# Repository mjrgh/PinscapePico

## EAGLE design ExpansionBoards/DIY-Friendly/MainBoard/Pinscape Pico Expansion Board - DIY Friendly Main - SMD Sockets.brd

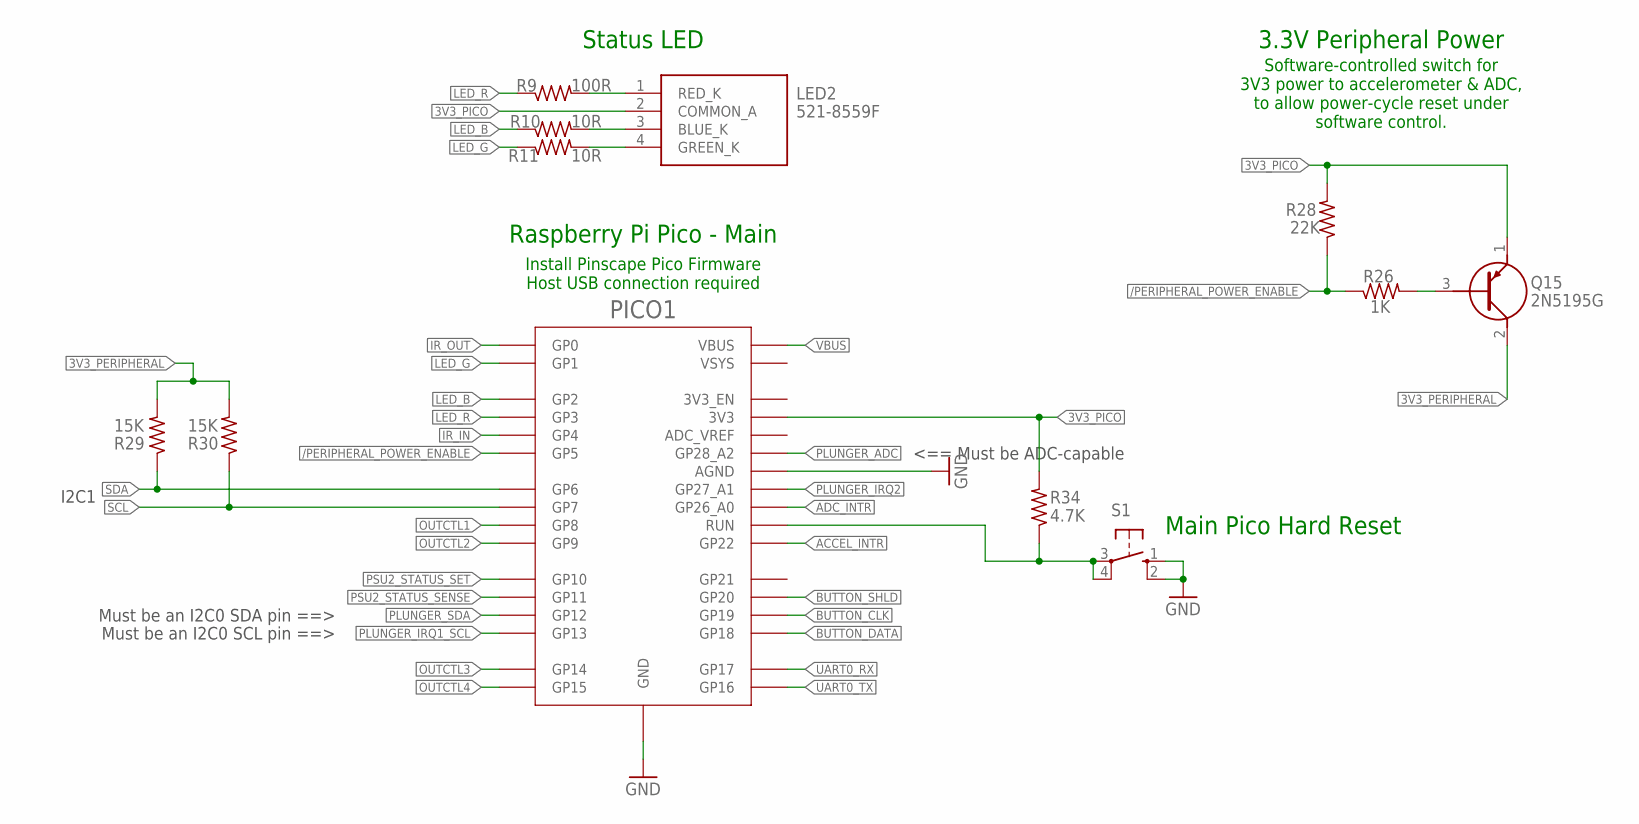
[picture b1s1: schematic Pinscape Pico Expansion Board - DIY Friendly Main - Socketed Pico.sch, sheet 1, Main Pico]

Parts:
LED2: 521-8559F; 5218559F
PICO1: RPI_PICO_NO_DEBUG; RPI_PICO_TH_NO_DEBUG
Q15: 2N5195G; TO229P300X760X1364-3P
R9: 100R; 0204/7; PARTNO 660-MFS1/4DCT52R47R0
R10, R11: 10R; 0204/7; PARTNO 660-MFS1/4DCT52R47R0
R26: 1K; 0204/7; PARTNO 660-MFS1/4DCT52R47R0
R28: 22K; 0204/7; PARTNO 660-MFS1/4DCT52R47R0
R29, R30: 15K; 0204/7; PARTNO 660-MFS1/4DCT52R47R0
R34: 4.7K; 0204/7; PARTNO 660-MFS1/4DCT52R47R0
S1: 10-XX; B3F-10XX

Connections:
3V3_PERIPHERAL: Q15.2 (C), R29.2, R30.2; also elsewhere on the board
3V3_PICO: LED2.2 (COMMON_A), PICO1.3V3, Q15.1 (E), R28.2, R34.2; also elsewhere on the board
LED_B: PICO1.GP2, R10.1; also elsewhere on the board
LED_G: PICO1.GP1, R11.1; also elsewhere on the board
LED_R: PICO1.GP3, R9.1; also elsewhere on the board
unnamed: LED2.1 (RED_K), R9.2
unnamed: Q15.3 (B), R26.2
unnamed: LED2.3 (BLUE_K), R10.2
unnamed: LED2.4 (GREEN_K), R11.2
UART0_RX: PICO1.GP17; also elsewhere on the board
UART0_TX: PICO1.GP16; also elsewhere on the board

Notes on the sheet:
Raspberry Pi Pico - Main
Must be an I2C0 SCL pin ==>
<== Must be ADC-capable
Must be an I2C0 SDA pin ==>
Main Pico Hard Reset
Status LED
3.3V Peripheral Power
Install Pinscape Pico Firmware Host USB connection required
I2C1
Software-controlled switch for 3V3 power to accelerometer & ADC, to allow power-cycle reset under software control.

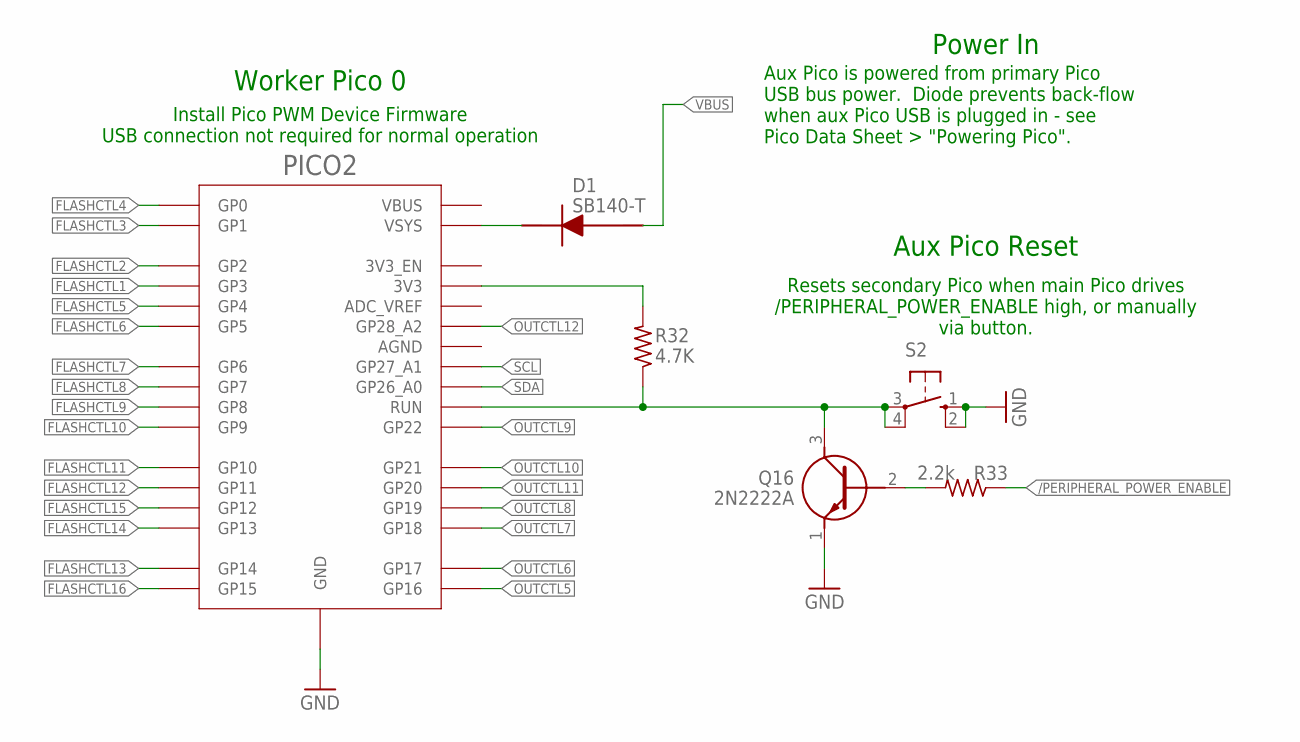
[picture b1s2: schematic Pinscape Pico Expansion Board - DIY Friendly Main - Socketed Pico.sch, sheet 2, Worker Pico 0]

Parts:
D1: SB140-T; DIOAD1408W86L464D236
PICO2: RPI_PICO_NO_DEBUG; RPI_PICO_TH_NO_DEBUG
Q16: 2N2222A
R32: 4.7K; 0204/7; PARTNO 660-MFS1/4DCT52R47R0
R33: 2.2k; 0204/7; PARTNO 660-MFS1/4DCT52R47R0
S2: 10-XX; B3F-10XX

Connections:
unnamed 103: D1.1 (K), PICO2.VSYS; also elsewhere on the board
unnamed: Q16.2 (B), R33.2
unnamed 120: PICO2.3V3, R32.2; also elsewhere on the board

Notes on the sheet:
Install Pico PWM Device Firmware USB connection not required for normal operation
Worker Pico 0
Aux Pico Reset
Resets secondary Pico when main Pico drives /PERIPHERAL_POWER_ENABLE high, or manually via button.
Aux Pico is powered from primary Pico USB bus power. Diode prevents back-flow when aux Pico USB is plugged in - see Pico Data Sheet > "Powering Pico".
Power In

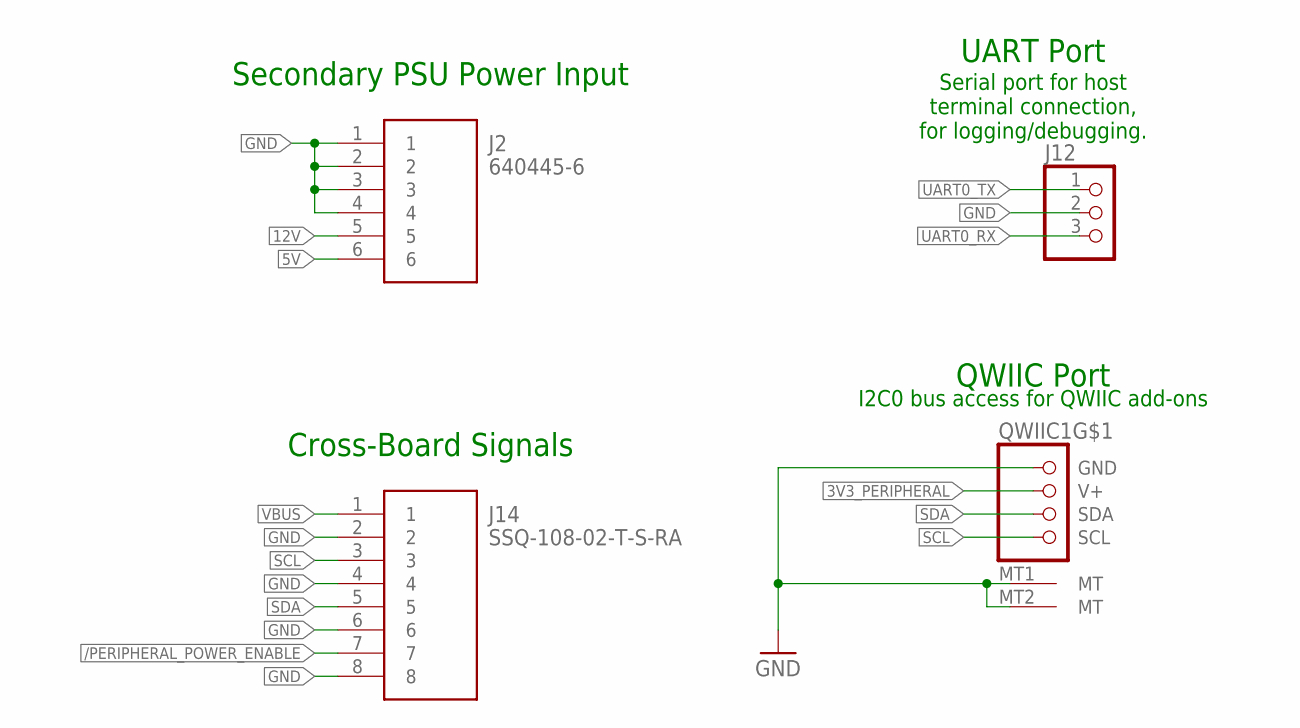
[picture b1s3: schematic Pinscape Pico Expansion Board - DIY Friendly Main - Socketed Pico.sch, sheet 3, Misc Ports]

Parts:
J2: 640445-6; SHDR6W183P0X396_1X6_2377X762X1
J12: PINHD-1X3; 1X03
J14: SSQ-108-02-T-S-RA; RHDRRA8W64P254_1X8_2083X851X24
QWIIC1: QWIIC; JST_SH4

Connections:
3V3_PERIPHERAL: QWIIC1.2 (V+); also elsewhere on the board
5V: J2.6; also elsewhere on the board
12V: J2.5; also elsewhere on the board
UART0_RX: J12.3; also elsewhere on the board
UART0_TX: J12.1; also elsewhere on the board

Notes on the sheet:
UART Port
Serial port for host terminal connection, for logging/debugging.
Secondary PSU Power Input
Cross-Board Signals
QWIIC Port
I2C0 bus access for QWIIC add-ons

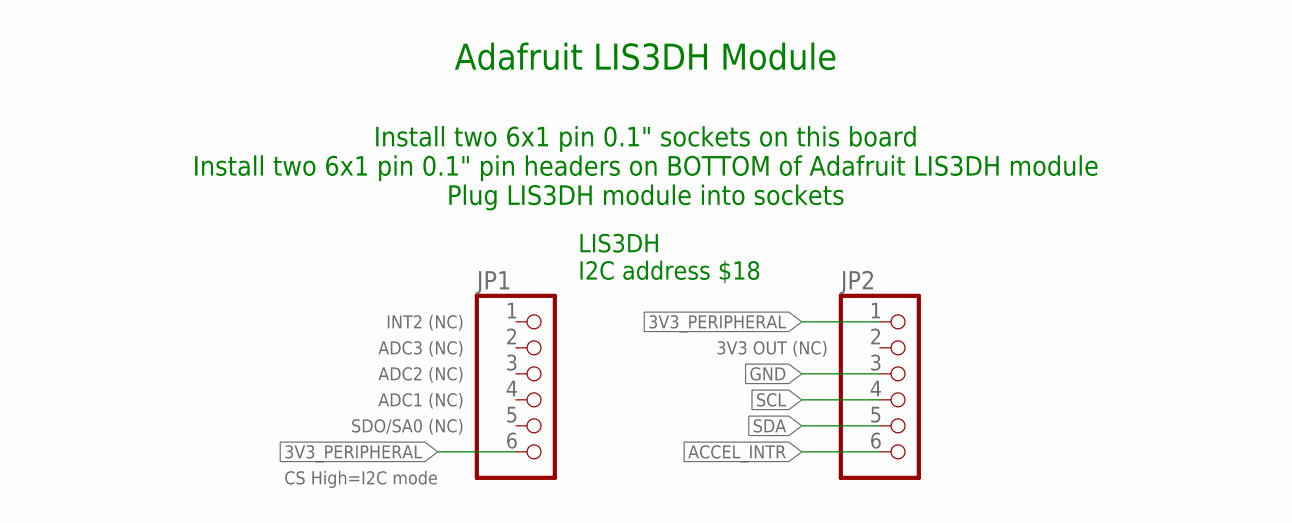
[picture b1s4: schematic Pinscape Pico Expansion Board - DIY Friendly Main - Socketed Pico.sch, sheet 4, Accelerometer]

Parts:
JP1, JP2: PINHD-1X6; 1X06

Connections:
3V3_PERIPHERAL: JP1.6, JP2.1; also elsewhere on the board
ACCEL_INTR: JP2.6; also elsewhere on the board

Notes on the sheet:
Adafruit LIS3DH Module
Install two 6x1 pin 0.1" sockets on this board Install two 6x1 pin 0.1" pin headers on BOTTOM of Adafruit LIS3DH module Plug LIS3DH module into sockets
INT2 (NC)
ADC3 (NC)
ADC2 (NC)
ADC1 (NC)
SDO/SA0 (NC)
3V3 OUT (NC)
LIS3DH I2C address $18
CS High=I2C mode

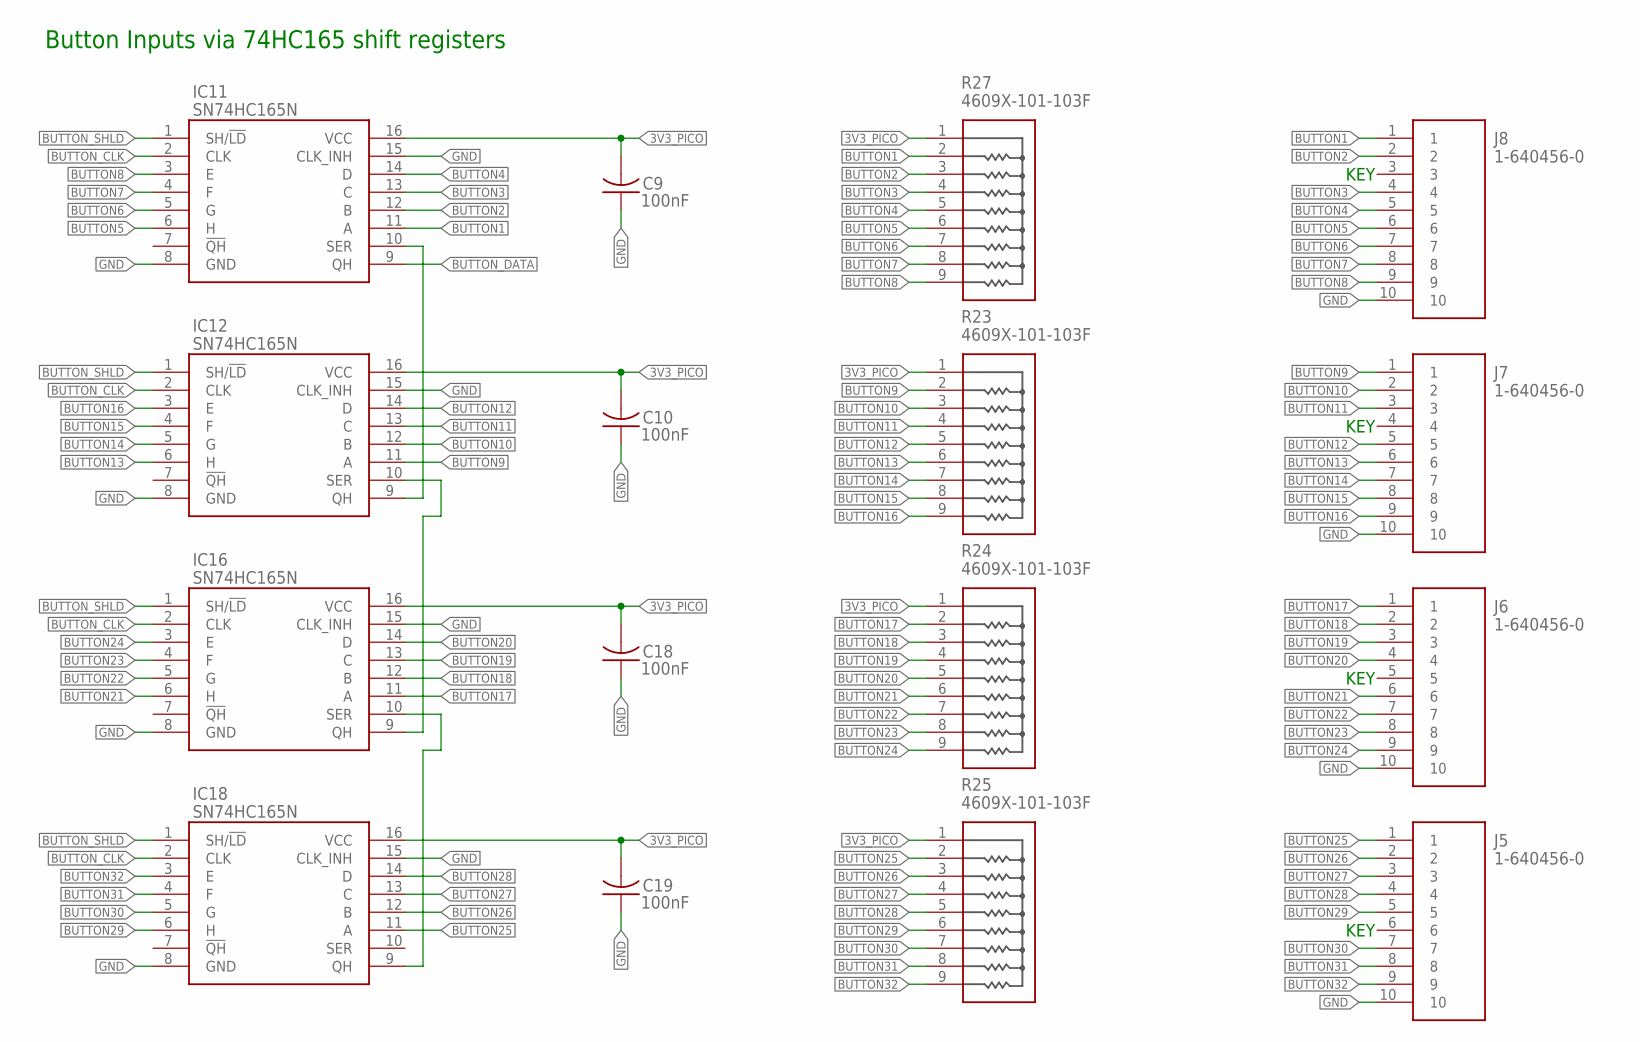
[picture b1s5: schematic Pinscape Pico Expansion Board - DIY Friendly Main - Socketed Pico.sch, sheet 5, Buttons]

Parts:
C9, C10, C18, C19: 100nF; C025-024X044; PARTNO 21RZ310-RC
IC11, IC12, IC16, IC18: SN74HC165N; DIP794W53P254L1930H508Q16N
J5, J6, J7, J8: 1-640456-0; SHDR10W66P0X254_1X10_2540X572X
R23, R24, R25, R27: 4609X-101-103F; 4609X

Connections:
3V3_PICO: C9.2, C10.2, C18.2, C19.2, IC11.16 (VCC), IC12.16 (VCC), IC16.16 (VCC), IC18.16 (VCC), R23.1, R24.1, R25.1, R27.1; also elsewhere on the board
BUTTON1: IC11.11 (A), J8.1, R27.2
BUTTON2: IC11.12 (B), J8.2, R27.3
BUTTON3: IC11.13 (C), J8.4, R27.4
BUTTON4: IC11.14 (D), J8.5, R27.5
BUTTON5: IC11.6 (H), J8.6, R27.6
BUTTON6: IC11.5 (G), J8.7, R27.7
BUTTON7: IC11.4 (F), J8.8, R27.8
BUTTON8: IC11.3 (E), J8.9, R27.9
BUTTON9: IC12.11 (A), J7.1, R23.2
BUTTON10: IC12.12 (B), J7.2, R23.3
BUTTON11: IC12.13 (C), J7.3, R23.4
BUTTON12: IC12.14 (D), J7.5, R23.5
BUTTON13: IC12.6 (H), J7.6, R23.6
BUTTON14: IC12.5 (G), J7.7, R23.7
BUTTON15: IC12.4 (F), J7.8, R23.8
BUTTON16: IC12.3 (E), J7.9, R23.9
BUTTON17: IC16.11 (A), J6.1, R24.2
BUTTON18: IC16.12 (B), J6.2, R24.3
BUTTON19: IC16.13 (C), J6.3, R24.4
BUTTON20: IC16.14 (D), J6.4, R24.5
BUTTON21: IC16.6 (H), J6.6, R24.6
BUTTON22: IC16.5 (G), J6.7, R24.7
BUTTON23: IC16.4 (F), J6.8, R24.8
BUTTON24: IC16.3 (E), J6.9, R24.9
BUTTON25: IC18.11 (A), J5.1, R25.2
BUTTON26: IC18.12 (B), J5.2, R25.3
BUTTON27: IC18.13 (C), J5.3, R25.4
BUTTON28: IC18.14 (D), J5.4, R25.5
BUTTON29: IC18.6 (H), J5.5, R25.6
BUTTON30: IC18.5 (G), J5.7, R25.7
BUTTON31: IC18.4 (F), J5.8, R25.8
BUTTON32: IC18.3 (E), J5.9, R25.9
BUTTON_CLK: IC11.2 (CLK), IC12.2 (CLK), IC16.2 (CLK), IC18.2 (CLK); also elsewhere on the board
BUTTON_DATA: IC11.9 (QH); also elsewhere on the board
BUTTON_SHLD: IC11.1 (SH/!LD), IC12.1 (SH/!LD), IC16.1 (SH/!LD), IC18.1 (SH/!LD); also elsewhere on the board
unnamed: IC11.10 (SER), IC12.9 (QH)
unnamed: IC12.10 (SER), IC16.9 (QH)
unnamed: IC16.10 (SER), IC18.9 (QH)

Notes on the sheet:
KEY
Button Inputs via 74HC165 shift registers

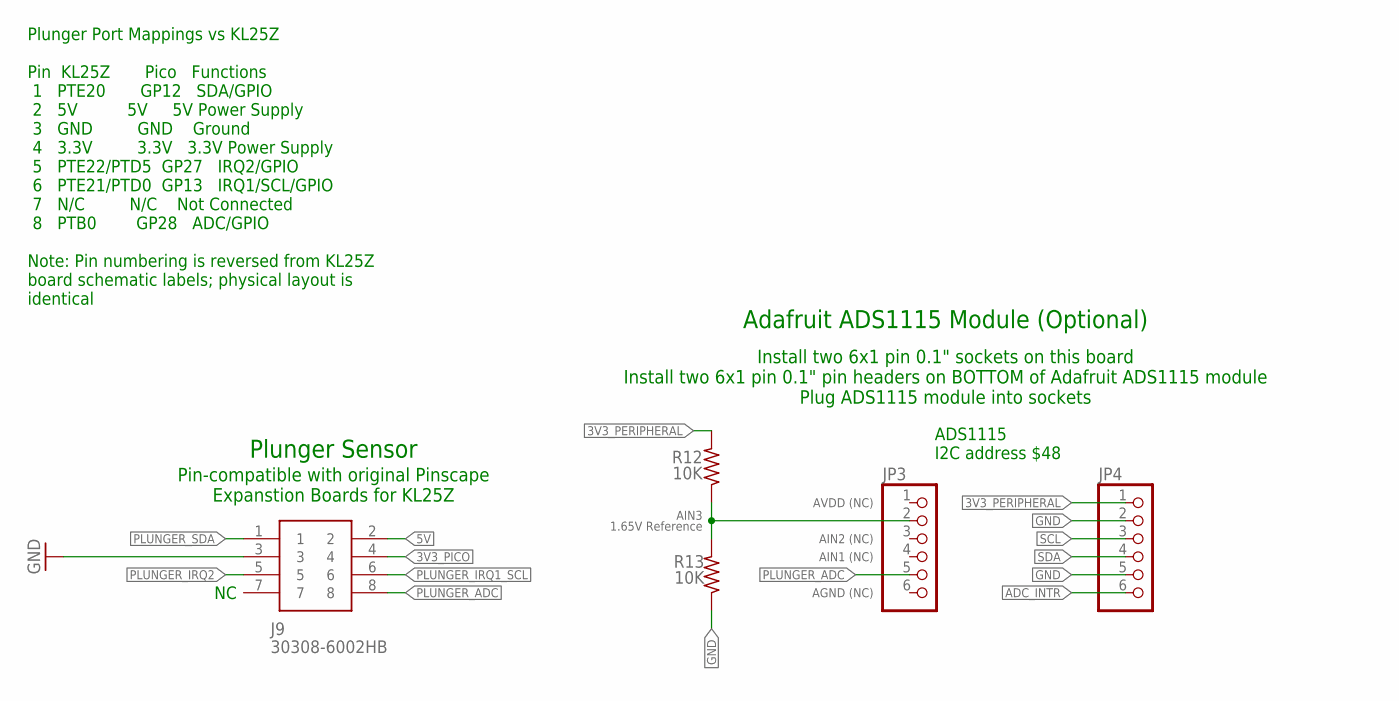
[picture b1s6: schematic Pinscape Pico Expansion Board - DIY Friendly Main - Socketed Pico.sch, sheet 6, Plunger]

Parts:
J9: 30308-6002HB; SHDR8W69P254_2X4_1780X878X955P
JP3, JP4: PINHD-1X6; 1X06
R12, R13: 10K; 0204/7; PARTNO 660-MFS1/4DCT52R47R0

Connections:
3V3_PERIPHERAL: JP4.1, R12.2; also elsewhere on the board
3V3_PICO: J9.4; also elsewhere on the board
5V: J9.2; also elsewhere on the board
ADC_INTR: JP4.6; also elsewhere on the board
unnamed: JP3.2, R12.1, R13.2
PLUNGER_ADC: J9.8, JP3.5; also elsewhere on the board
PLUNGER_IRQ1_SCL: J9.6; also elsewhere on the board
PLUNGER_IRQ2: J9.5; also elsewhere on the board
PLUNGER_SDA: J9.1; also elsewhere on the board

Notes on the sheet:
Plunger Sensor
Adafruit ADS1115 Module (Optional)
Install two 6x1 pin 0.1" sockets on this board Install two 6x1 pin 0.1" pin headers on BOTTOM of Adafruit ADS1115 module Plug ADS1115 module into sockets
AVDD (NC)
AGND (NC)
AIN3 1.65V Reference
AIN2 (NC)
AIN1 (NC)
Pin-compatible with original Pinscape Expanstion Boards for KL25Z
ADS1115 I2C address $48
Plunger Port Mappings vs KL25Z Pin KL25Z Pico Functions 1 PTE20 GP12 SDA/GPIO 2 5V 5V 5V Power Supply 3 GND GND Ground 4 3.3V 3.3V 3.3V Power Supply 5 PTE22/PTD5 GP27 IRQ2/GPIO 6 PTE21/PTD0 GP13 IRQ1/SCL/GPIO 7 N/C N/C Not Connected 8 PTB0 GP28 ADC/GPIO Note: Pin numbering is reversed from KL25Z bo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

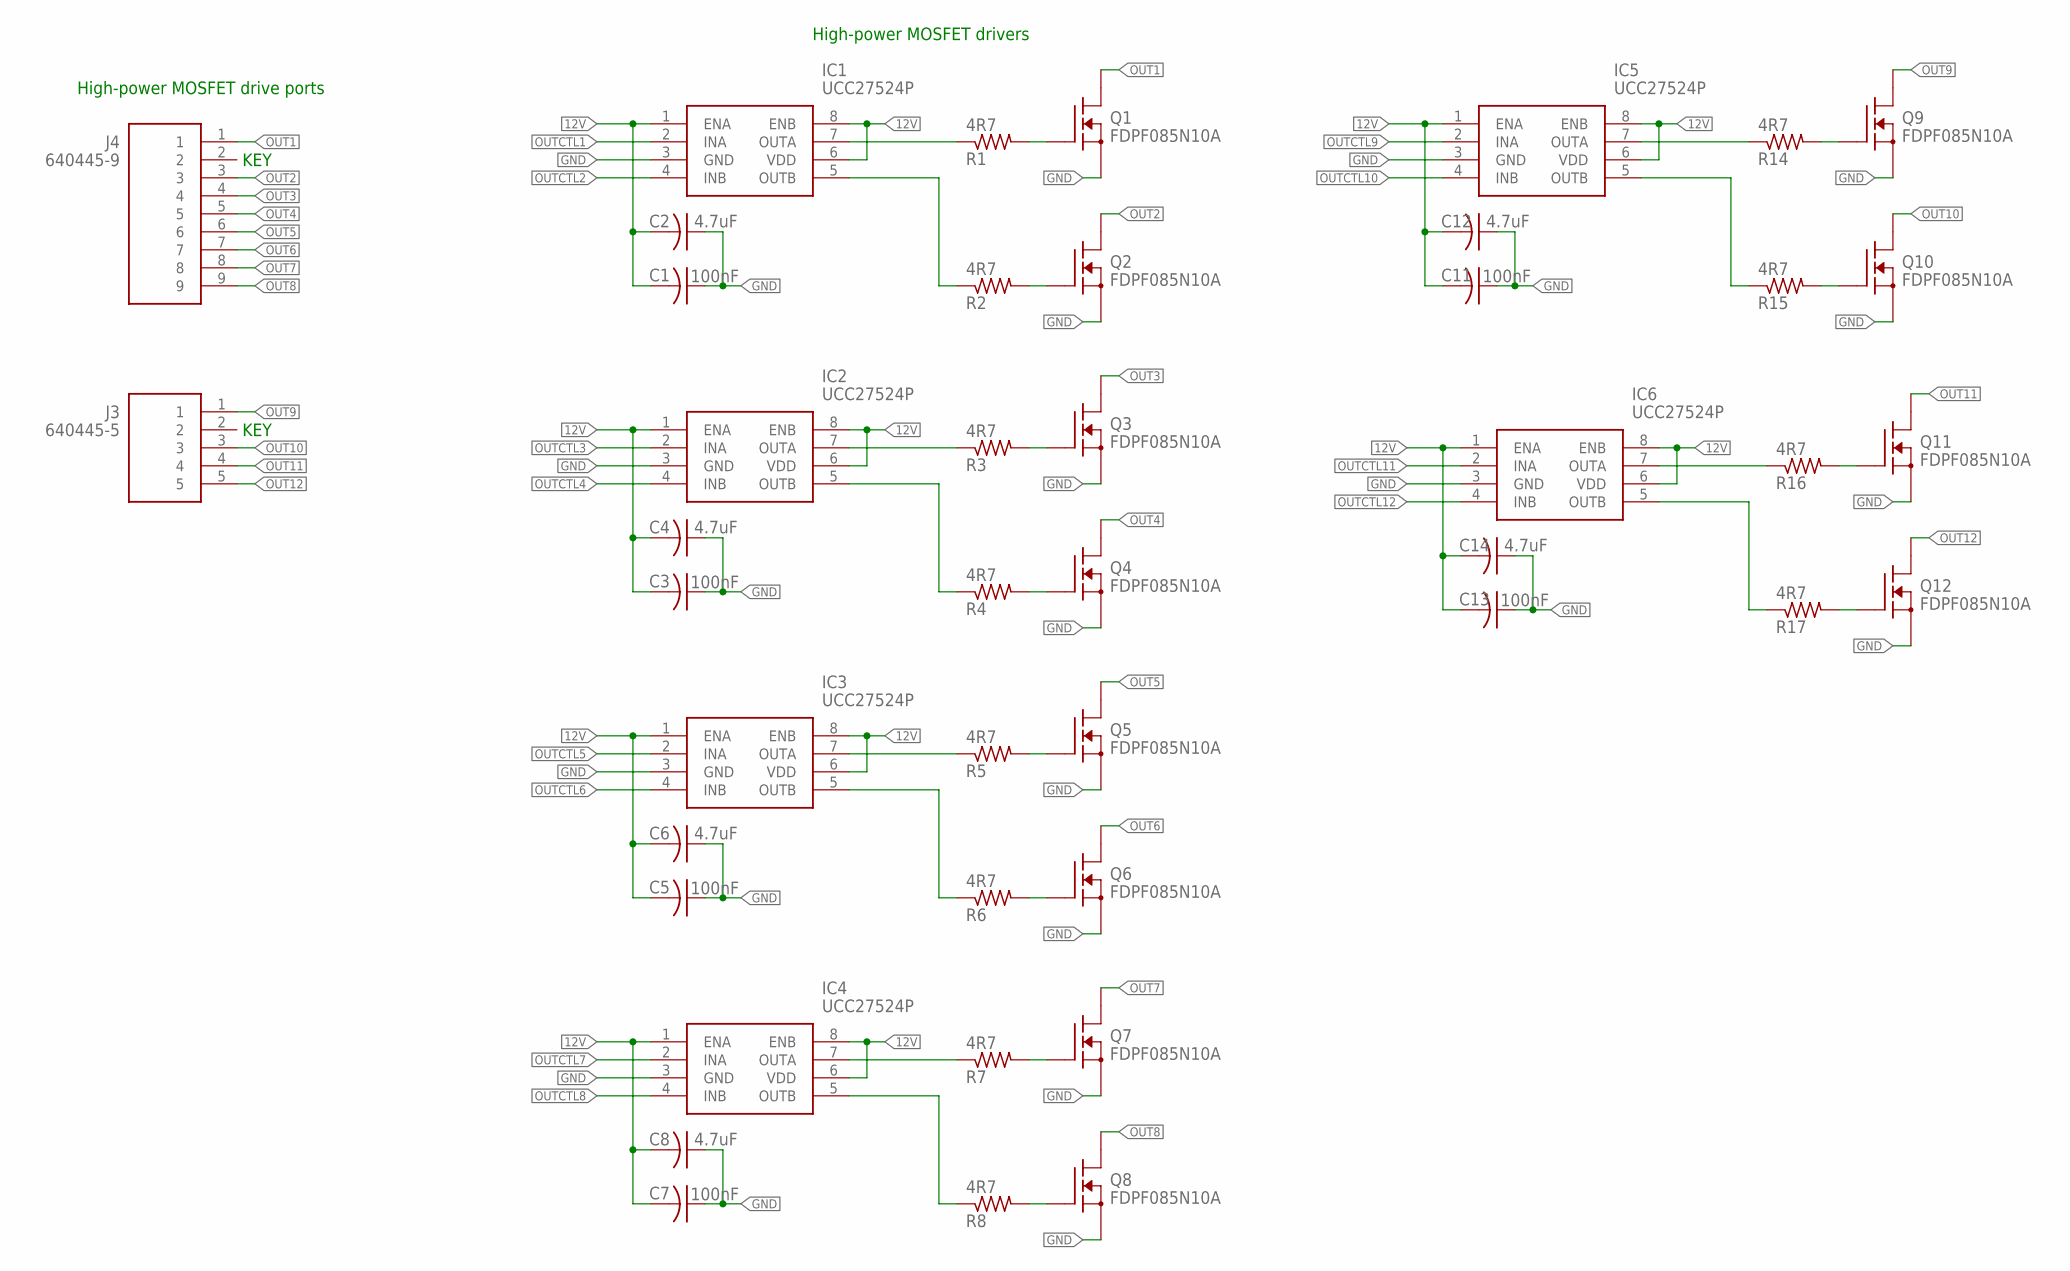
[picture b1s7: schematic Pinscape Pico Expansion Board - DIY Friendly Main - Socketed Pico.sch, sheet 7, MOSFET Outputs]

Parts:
C1, C3, C5, C7, C11, C13: 100nF; C025-024X044; PARTNO 21RZ310-RC
C2, C4, C6, C8, C12, C14: 4.7uF; C025-024X044; PARTNO 810-FG14X5R1H475KRT0
IC1, IC2, IC3, IC4, IC5, IC6: UCC27524P; DIP794W53P254L959H508Q8N
J3: 640445-5; HDRV5W117P0X396_1X5_1981X762X1
J4: 640445-9; SHDR9W117P0X396_1X9_3566X762X1
Q1, Q2, Q3, Q4, Q5, Q6, Q7, Q8, Q9, Q10, Q11, Q12: FDPF085N10A; TO220BV; PARTNO FDPF085N10A
R1, R2, R3, R4, R5, R6, R7, R8, R14, R15, R16, R17: 4R7; 0204/5; PARTNO 660-MFS1/4DCT52R47R0

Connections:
12V: C1.2, C2.2, C3.2, C4.2, C5.2, C6.2, C7.2, C8.2, C11.2, C12.2, C13.2, C14.2, IC1.1 (ENA), IC1.6 (VDD), IC1.8 (ENB), IC2.1 (ENA), IC2.6 (VDD), IC2.8 (ENB), IC3.1 (ENA), IC3.6 (VDD), IC3.8 (ENB), IC4.1 (ENA), IC4.6 (VDD), IC4.8 (ENB), IC5.1 (ENA), IC5.6 (VDD), IC5.8 (ENB), IC6.1 (ENA), IC6.6 (VDD), IC6.8 (ENB); also elsewhere on the board
unnamed: IC1.7 (OUTA), R1.1
unnamed: IC1.5 (OUTB), R2.1
unnamed: Q1.1 (G), R1.2
unnamed: Q2.1 (G), R2.2
unnamed: IC2.7 (OUTA), R3.1
unnamed: IC2.5 (OUTB), R4.1
unnamed: Q3.1 (G), R3.2
unnamed: Q4.1 (G), R4.2
unnamed: IC3.7 (OUTA), R5.1
unnamed: IC3.5 (OUTB), R6.1
unnamed: Q5.1 (G), R5.2
unnamed: Q6.1 (G), R6.2
unnamed: IC4.7 (OUTA), R7.1
unnamed: IC4.5 (OUTB), R8.1
unnamed: Q7.1 (G), R7.2
unnamed: Q8.1 (G), R8.2
unnamed: IC5.7 (OUTA), R14.1
unnamed: IC5.5 (OUTB), R15.1
unnamed: Q9.1 (G), R14.2
unnamed: Q10.1 (G), R15.2
unnamed: IC6.7 (OUTA), R16.1
unnamed: IC6.5 (OUTB), R17.1
unnamed: Q11.1 (G), R16.2
unnamed: Q12.1 (G), R17.2
OUT1: J4.1, Q1.2 (D)
OUT2: J4.3, Q2.2 (D)
OUT3: J4.4, Q3.2 (D)
OUT4: J4.5, Q4.2 (D)
OUT5: J4.6, Q5.2 (D)
OUT6: J4.7, Q6.2 (D)
OUT7: J4.8, Q7.2 (D)
OUT8: J4.9, Q8.2 (D)
OUT9: J3.1, Q9.2 (D)
OUT10: J3.3, Q10.2 (D)
OUT11: J3.4, Q11.2 (D)
OUT12: J3.5, Q12.2 (D)
OUTCTL1: IC1.2 (INA); also elsewhere on the board
OUTCTL2: IC1.4 (INB); also elsewhere on the board
OUTCTL3: IC2.2 (INA); also elsewhere on the board
OUTCTL4: IC2.4 (INB); also elsewhere on the board
OUTCTL5: IC3.2 (INA); also elsewhere on the board
OUTCTL6: IC3.4 (INB); also elsewhere on the board
OUTCTL7: IC4.2 (INA); also elsewhere on the board
OUTCTL8: IC4.4 (INB); also elsewhere on the board
OUTCTL9: IC5.2 (INA); also elsewhere on the board
OUTCTL10: IC5.4 (INB); also elsewhere on the board
OUTCTL11: IC6.2 (INA); also elsewhere on the board
OUTCTL12: IC6.4 (INB); also elsewhere on the board

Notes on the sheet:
High-power MOSFET drive ports
KEY
High-power MOSFET drivers

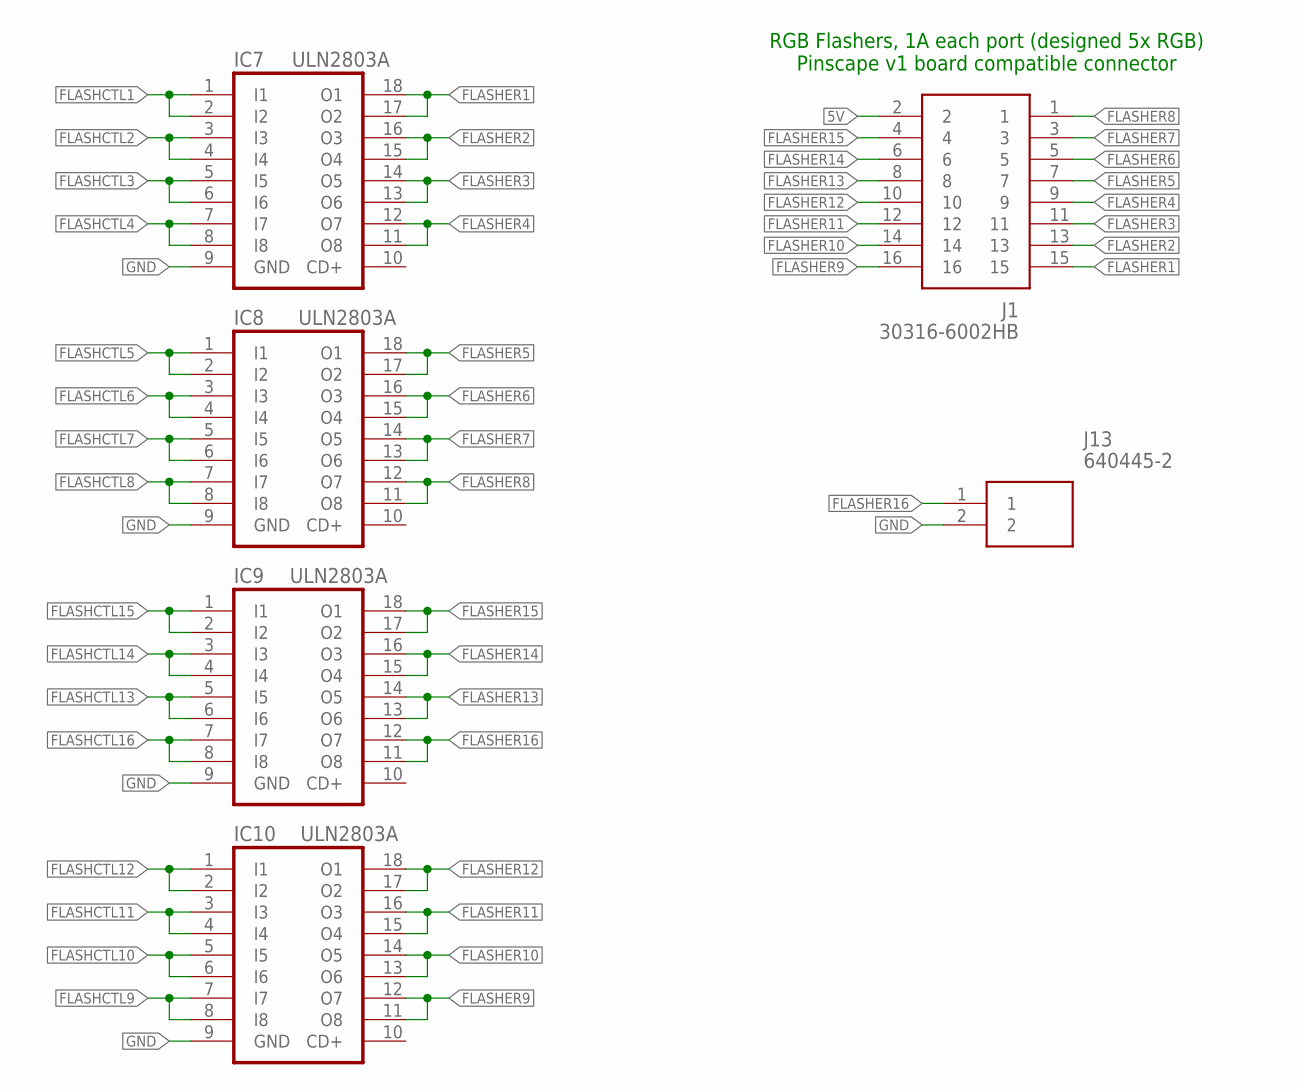
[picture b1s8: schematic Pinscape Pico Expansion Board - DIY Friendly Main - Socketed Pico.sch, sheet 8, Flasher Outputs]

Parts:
IC7, IC8, IC9, IC10: ULN2803A; DIL18
J1: 30316-6002HB; 3M-30316-6002HB
J13: 640445-2; SHDR2W117P0X396_1X2_792X762X11

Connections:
5V: J1.2; also elsewhere on the board
FLASHCTL1: IC7.1 (I1), IC7.2 (I2); also elsewhere on the board
FLASHCTL2: IC7.3 (I3), IC7.4 (I4); also elsewhere on the board
FLASHCTL3: IC7.5 (I5), IC7.6 (I6); also elsewhere on the board
FLASHCTL4: IC7.7 (I7), IC7.8 (I8); also elsewhere on the board
FLASHCTL5: IC8.1 (I1), IC8.2 (I2); also elsewhere on the board
FLASHCTL6: IC8.3 (I3), IC8.4 (I4); also elsewhere on the board
FLASHCTL7: IC8.5 (I5), IC8.6 (I6); also elsewhere on the board
FLASHCTL8: IC8.7 (I7), IC8.8 (I8); also elsewhere on the board
FLASHCTL9: IC10.7 (I7), IC10.8 (I8); also elsewhere on the board
FLASHCTL10: IC10.5 (I5), IC10.6 (I6); also elsewhere on the board
FLASHCTL11: IC10.3 (I3), IC10.4 (I4); also elsewhere on the board
FLASHCTL12: IC10.1 (I1), IC10.2 (I2); also elsewhere on the board
FLASHCTL13: IC9.5 (I5), IC9.6 (I6); also elsewhere on the board
FLASHCTL14: IC9.3 (I3), IC9.4 (I4); also elsewhere on the board
FLASHCTL15: IC9.1 (I1), IC9.2 (I2); also elsewhere on the board
FLASHCTL16: IC9.7 (I7), IC9.8 (I8); also elsewhere on the board
FLASHER1: IC7.17 (O2), IC7.18 (O1), J1.15
FLASHER2: IC7.15 (O4), IC7.16 (O3), J1.13
FLASHER3: IC7.13 (O6), IC7.14 (O5), J1.11
FLASHER4: IC7.11 (O8), IC7.12 (O7), J1.9
FLASHER5: IC8.17 (O2), IC8.18 (O1), J1.7
FLASHER6: IC8.15 (O4), IC8.16 (O3), J1.5
FLASHER7: IC8.13 (O6), IC8.14 (O5), J1.3
FLASHER8: IC8.11 (O8), IC8.12 (O7), J1.1
FLASHER9: IC10.11 (O8), IC10.12 (O7), J1.16
FLASHER10: IC10.13 (O6), IC10.14 (O5), J1.14
FLASHER11: IC10.15 (O4), IC10.16 (O3), J1.12
FLASHER12: IC10.17 (O2), IC10.18 (O1), J1.10
FLASHER13: IC9.13 (O6), IC9.14 (O5), J1.8
FLASHER14: IC9.15 (O4), IC9.16 (O3), J1.6
FLASHER15: IC9.17 (O2), IC9.18 (O1), J1.4
FLASHER16: IC9.11 (O8), IC9.12 (O7), J13.1

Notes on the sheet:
RGB Flashers, 1A each port (designed 5x RGB) Pinscape v1 board compatible connector

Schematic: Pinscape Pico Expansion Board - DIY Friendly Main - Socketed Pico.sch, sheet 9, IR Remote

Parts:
C16: 4.7uF; C025-024X044; PARTNO 810-FG14X5R1H475KRT0
D3, D4: 1N4148; DO35-7
J10: 215079-4; 2150794
J11: 640454-2; HDRV2W66P0X254_1X2_762X572X100
Q13: BC337-25; BC33725
R19: 1.8K; 0204/7; PARTNO 660-MFS1/4DCT52R47R0
R31: 2R5; 0204/7; PARTNO 660-MFS1/4DCT52R47R0

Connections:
3V3_PICO: J10.1; also elsewhere on the board
5V: C16.1, J11.1; also elsewhere on the board
$N377: D3.A, Q13.2 (B), R19.2
IR_IN: J10.3; also elsewhere on the board
IR_LED_CATHODE: J11.2, Q13.1 (C)
IR_OUT: R19.1; also elsewhere on the board
unnamed: D3.C, D4.A
unnamed: Q13.3 (E), R31.2

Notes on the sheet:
IR REMOTE CONTROL TRANSMITTER Use with TSAL6400 IRED or equivalent, with a peak wavelength around 940nm. Set the current-sense resistor according to the desired forward current on the IR LED. The IR LED should be connected directly to the header (no external resistor is needed). Two IR LEDs can be 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
IR REMOTE RECEIVER CONNECTOR This header allows connecting an IR receiver (TSOP38438) on a separate circuit board, connected to the main board with a 4-conductor ribbon cable. The board should include the VCC supply filter circuit (220R + 150nF) shown in the data sheet.
===> IRED Cathode (-)
===> IRED Anode (+)
Note: TE Connectivity Micro-Match 215079-4 base pairs with 215083-4 on-cable IDC connector.
Resistor sets current to I(LED) = 0.5V/R R=2.5 ohms -> 200mA current
NPN substitutes: choose any medium-power NPN with Hfe around 100
IR EMITTER / IR RECEIVER The emitter and receiver are designed to be installed remotely to allow placing them in suitable line-of-sight locations.

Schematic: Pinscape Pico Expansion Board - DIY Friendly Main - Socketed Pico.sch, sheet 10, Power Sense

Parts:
C15: 100nF; C025-024X044; PARTNO 21RZ310-RC
IC13: SN74HC74NE4; DIP794W53P254L1930H508Q14N
IC14: PC827; DIL08
IC15: S-80833CLY; TO-92_(TO-226)
R18: 240R; 0204/7; PARTNO 660-MFS1/4DCT52R47R0
R20, R22: 10K; 0204/7; PARTNO 660-MFS1/4DCT52R47R0
R21: 360R; 0204/7; PARTNO 660-MFS1/4DCT52R47R0

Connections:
3V3_PICO: IC14.6 (COL); also elsewhere on the board
5V: C15.1, IC13.2 (1D), IC13.4 (1!PRE), IC13.14 (VCC), IC14.8 (COL), IC15.2 (VDD); also elsewhere on the board
unnamed: IC13.3 (1CLK), IC14.7 (EMIT), R20.1
unnamed: IC14.2 (C), R18.2
unnamed: IC13.1 (!1CLR), IC15.1 (OUT)
unnamed: IC14.4 (C), R21.2
unnamed: IC13.5 (1Q), IC14.3 (A)
PSU2_STATUS_SENSE: IC14.5 (EMIT), R22.2; also elsewhere on the board
PSU2_STATUS_SET: IC14.1 (A); also elsewhere on the board

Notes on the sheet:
PSU2 Power Sensing This circuit monitors the status of a secondary power supply (PSU2) that's hard-switched on and off with the overall pinball cabinet power. The status circuit maintains its own memory of the power state, independently of the Pico's power state, which satisfies two important condi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
POR part selection: The POR is triggered by the voltage on the 5V supply crossing a threshold voltage, so we must choose a POR whose threshold voltage slightly below the MINIMUM voltage that the 5V supply maintains when powered on and operating stably. Nominally, this would be 4.75V for an ATX supp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
Note: RESET signal must be ACTIVE LOW

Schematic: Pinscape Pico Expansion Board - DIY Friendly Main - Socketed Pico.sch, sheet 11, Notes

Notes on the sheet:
I2C Address Map (7-bit notation) $18 LIS3DH (Accelerometer) $30 Pico PWM Helper (main board) $31 Pico PWM Helper #1 (power board) $32 Pico PWM Helper #2 (power board) $48 ADS1115 (ADC) $68 DS1307 (RTC clock/calendar chip) [On Power board]

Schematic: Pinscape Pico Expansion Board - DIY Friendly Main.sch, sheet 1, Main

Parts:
D1: SB140-T; DIOAD1408W86L464D236
D2: 1N5711; DIOAD1084W56L378D176
J2: 640445-6; SHDR6W183P0X396_1X6_2377X762X1
J12: PINHD-1X3; 1X03
J14: PINHD-1X8/90; 1X08/90
LED2: 521-8559F; 5218559F
PICO1, PICO2: RPI_PICO-SMD; RPI_PICO
Q15: 2N5195G; TO229P300X760X1364-3P
Q16: 2N2222A
QWIIC1: QWIIC; JST_SH4
R9: 100R; 0204/7; PARTNO 660-MFS1/4DCT52R47R0
R10, R11: 10R; 0204/7; PARTNO 660-MFS1/4DCT52R47R0
R26: 1K; 0204/7; PARTNO 660-MFS1/4DCT52R47R0
R28: 22K; 0204/7; PARTNO 660-MFS1/4DCT52R47R0
R29, R30: 15K; 0204/5; PARTNO 660-MFS1/4DCT52R47R0
R32: 2.2K; 0204/7; PARTNO 660-MFS1/4DCT52R47R0
R33: 2.2k; 0204/7; PARTNO 660-MFS1/4DCT52R47R0
S1: 10-XX; B3F-10XX

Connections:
3V3_PERIPHERAL: Q15.2 (C), QWIIC1.2 (V+), R29.2, R30.2; also elsewhere on the board
3V3_PICO: LED2.2 (COMMON_A), PICO1.3V3, Q15.1 (E), R28.2; also elsewhere on the board
5V: J2.6; also elsewhere on the board
12V: J2.5; also elsewhere on the board
LED_B: PICO1.GP2, R10.1; also elsewhere on the board
LED_G: PICO1.GP1, R11.1; also elsewhere on the board
LED_R: PICO1.GP3, R9.1; also elsewhere on the board
unnamed 103: D1.1 (K), PICO2.VSYS; also elsewhere on the board
unnamed: LED2.1 (RED_K), R9.2
unnamed: Q15.3 (B), R26.2
unnamed: Q16.2 (B), R33.2
unnamed 120: PICO2.3V3, R32.2; also elsewhere on the board
unnamed: LED2.3 (BLUE_K), R10.2
unnamed: LED2.4 (GREEN_K), R11.2
UART0_RX: J12.3, PICO1.GP17; also elsewhere on the board
UART0_TX: J12.1, PICO1.GP16; also elsewhere on the board

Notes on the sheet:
Raspberry Pi Pico - Main
Must be an I2C0 SCL pin ==>
<== Must be ADC-capable
Must be an I2C0 SDA pin ==>
Install Pico PWM Device Firmware USB connection not required for normal operation
UART Port
Serial port for host terminal connection, for logging/debugging.
Worker Pico
Pico Hard Reset
Status LED
Secondary PSU Power Input
Cross-Board Signals
3.3V Peripheral Power
Install Pinscape Pico Firmware Host USB connection required
Aux Pico Reset
Resets secondary Picos by pulling /AUX_RESET LOW on /RESET low OR /PERIPHERAL_POWER_ENABLE high.
QWIIC Port
I2C0 bus access for QWIIC add-ons
I2C1

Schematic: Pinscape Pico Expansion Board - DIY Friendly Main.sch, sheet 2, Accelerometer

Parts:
JP1, JP2: PINHD-1X6; 1X06

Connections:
3V3_PERIPHERAL: JP1.6, JP2.1; also elsewhere on the board
ACCEL_INTR: JP2.6; also elsewhere on the board

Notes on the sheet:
Adafruit LIS3DH Module
Install two 6x1 pin 0.1" sockets on this board Install two 6x1 pin 0.1" pin headers on BOTTOM of Adafruit LIS3DH module Plug LIS3DH module into sockets
INT2 (NC)
ADC3 (NC)
ADC2 (NC)
ADC1 (NC)
SDO/SA0 (NC)
3V3 OUT (NC)
LIS3DH I2C address $18
CS High=I2C mode

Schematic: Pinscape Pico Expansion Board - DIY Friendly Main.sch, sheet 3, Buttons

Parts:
C9, C10, C18, C19: 100nF; C025-024X044; PARTNO 21RZ310-RC
IC11, IC12, IC16, IC18: SN74HC165N; DIP794W53P254L1930H508Q16N
J5, J6, J7, J8: 1-640456-0; SHDR10W66P0X254_1X10_2540X572X
R23, R24, R25, R27: 4609X-101-103F; 4609X

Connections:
3V3_PICO: C9.2, C10.2, C18.2, C19.2, IC11.16 (VCC), IC12.16 (VCC), IC16.16 (VCC), IC18.16 (VCC), R23.1, R24.1, R25.1, R27.1; also elsewhere on the board
BUTTON1: IC11.11 (A), J8.1, R27.2
BUTTON2: IC11.12 (B), J8.2, R27.3
BUTTON3: IC11.13 (C), J8.4, R27.4
BUTTON4: IC11.14 (D), J8.5, R27.5
BUTTON5: IC11.6 (H), J8.6, R27.6
BUTTON6: IC11.5 (G), J8.7, R27.7
BUTTON7: IC11.4 (F), J8.8, R27.8
BUTTON8: IC11.3 (E), J8.9, R27.9
BUTTON9: IC12.11 (A), J7.1, R23.2
BUTTON10: IC12.12 (B), J7.2, R23.3
BUTTON11: IC12.13 (C), J7.3, R23.4
BUTTON12: IC12.14 (D), J7.5, R23.5
BUTTON13: IC12.6 (H), J7.6, R23.6
BUTTON14: IC12.5 (G), J7.7, R23.7
BUTTON15: IC12.4 (F), J7.8, R23.8
BUTTON16: IC12.3 (E), J7.9, R23.9
BUTTON17: IC16.11 (A), J6.1, R24.2
BUTTON18: IC16.12 (B), J6.2, R24.3
BUTTON19: IC16.13 (C), J6.3, R24.4
BUTTON20: IC16.14 (D), J6.4, R24.5
BUTTON21: IC16.6 (H), J6.6, R24.6
BUTTON22: IC16.5 (G), J6.7, R24.7
BUTTON23: IC16.4 (F), J6.8, R24.8
BUTTON24: IC16.3 (E), J6.9, R24.9
BUTTON25: IC18.11 (A), J5.1, R25.2
BUTTON26: IC18.12 (B), J5.2, R25.3
BUTTON27: IC18.13 (C), J5.3, R25.4
BUTTON28: IC18.14 (D), J5.4, R25.5
BUTTON29: IC18.6 (H), J5.5, R25.6
BUTTON30: IC18.5 (G), J5.7, R25.7
BUTTON31: IC18.4 (F), J5.8, R25.8
BUTTON32: IC18.3 (E), J5.9, R25.9
BUTTON_CLK: IC11.2 (CLK), IC12.2 (CLK), IC16.2 (CLK), IC18.2 (CLK); also elsewhere on the board
BUTTON_DATA: IC11.9 (QH); also elsewhere on the board
BUTTON_SHLD: IC11.1 (SH/!LD), IC12.1 (SH/!LD), IC16.1 (SH/!LD), IC18.1 (SH/!LD); also elsewhere on the board
unnamed: IC11.10 (SER), IC12.9 (QH)
unnamed: IC12.10 (SER), IC16.9 (QH)
unnamed: IC16.10 (SER), IC18.9 (QH)

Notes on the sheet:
KEY
Button Inputs via 74HC165 shift registers

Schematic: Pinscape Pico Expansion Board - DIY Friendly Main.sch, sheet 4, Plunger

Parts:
J9: 30308-6002HB; SHDR8W69P254_2X4_1780X878X955P
JP3, JP4: PINHD-1X6; 1X06
R12, R13: 10K; 0204/7; PARTNO 660-MFS1/4DCT52R47R0

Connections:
3V3_PERIPHERAL: JP4.1, R12.2; also elsewhere on the board
3V3_PICO: J9.4; also elsewhere on the board
5V: J9.2; also elsewhere on the board
ADC_INTR: JP4.6; also elsewhere on the board
unnamed: JP3.2, R12.1, R13.2
PLUNGER_ADC: J9.8, JP3.5; also elsewhere on the board
PLUNGER_IRQ1_SCL: J9.6; also elsewhere on the board
PLUNGER_IRQ2: J9.5; also elsewhere on the board
PLUNGER_SDA: J9.1; also elsewhere on the board

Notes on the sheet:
Plunger Sensor
Adafruit ADS1115 Module (Optional)
Install two 6x1 pin 0.1" sockets on this board Install two 6x1 pin 0.1" pin headers on BOTTOM of Adafruit ADS1115 module Plug ADS1115 module into sockets
AVDD (NC)
AGND (NC)
AIN3 1.65V Reference
AIN2 (NC)
AIN1 (NC)
Pin-compatible with original Pinscape Expanstion Boards for KL25Z
ADS1115 I2C address $48
Plunger Port Mappings vs KL25Z Pin KL25Z Pico Functions 1 PTE20 GP12 SDA/GPIO 2 5V 5V 5V Power Supply 3 GND GND Ground 4 3.3V 3.3V 3.3V Power Supply 5 PTE22/PTD5 GP10 IRQ2/GPIO 6 PTE21/PTD0 GP13 IRQ1/SCL/GPIO 7 N/C N/C Not Connected 8 PTB0 GP28 ADC/GPIO Note: Pin numbering is reversed from KL25Z bo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
